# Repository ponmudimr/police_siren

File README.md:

## My 5-Day Launch into PCB Design 🚀

This project was a rapid, hands-on journey from theory to a physical product. Here's a log of how I designed and built my first custom PCB from scratch, with photos from each stage of the process.

---

### **Day 1: Unlocking the Lab! 🔑**
The journey began by conquering the basics. I passed the foundational electronics tests, which felt like beating a final boss to unlock the ultimate prize: **full access to the PCB & Fabrication lab**. The real adventure was about to start.

---

### **Day 2: Discovering the World of PCBs 💡**
Next, I dove into the theory of **Printed Circuit Boards (PCBs)**. I learned how these essential components are the hidden skeletons inside every gadget we use, providing the foundation for all the electronics.

---

### **Day 3: Architecting the Schematic 📝**
It was time to become an architect for electricity. Using **KiCad**, I designed the **schematic layout**. This is the foundational blueprint that shows how every single component connects logically, serving as the master plan for the circuit.

*The final schematic design for the police siren circuit.*

---

### **Day 4: Drawing the Copper Highways 🗺️**
With the blueprint done, I moved on to the physical design. This involved assigning **footprints** (the physical pads where components will sit) and then carefully routing the **traces** (the copper pathways connecting them). This is where the board takes its final shape.

*The final PCB layout in KiCad, showing all the copper traces ready for fabrication.*

---

### **Day 5: The Magic of Fabrication 🔥**
This was the most exciting part! I took my finished design files to the lab and watched as the machine **fabricated the board**. Seeing a digital design get etched into a physical copper-clad board was the perfect reward for all the hard work.

*The freshly fabricated board, ready for soldering!*

---

### **Day 6: Assembly, Soldering & Testing 🛠️⚡**

After fabrication, it was time to bring my design to life!  
Before soldering the components, I practiced on a dot board to get better control over my iron and verify the circuit’s working.

*My practice prototype on a dot board, which helped me verify the circuit and improve my soldering skills.*

Once confident, I moved on to the actual PCB and soldered each component — **resistors, LEDs, ICs, capacitors** — with precision and care.  
After assembly, I powered it on for the first test… and the **LEDs blinked perfectly** as per my design! That moment proved every step of the process was successful.

*The final assembled PCB after soldering — fully functional and glowing LEDs!*

---

### **Results Summary ✅**

| Stage | Status | Description |
|:------|:--------|:------------|
| Schematic Design | ✔️ | Completed in KiCad |
| PCB Layout | ✔️ | Verified with DRC |
| Fabrication | ✔️ | Successfully etched and drilled |
| Soldering | ✔️ | Components soldered neatly |
| Testing | ⚡ | Circuit fully functional |

---

### **What I Learned 🧠**

- PCB Design workflow using **KiCad**  
- Component placement, routing, and layout rules  
- Hands-on **fabrication and soldering techniques**  
- Debugging circuits and verifying outputs  
- How patience and precision make great PCBs  

---

### **Next Step 🔮**
This is just the beginning! I’m planning to:  
- Add a **microcontroller (Arduino/ATtiny)** for programmable siren patterns  
- Integrate **sound output**  
- Try designing a **double-layer PCB**

---

> “From schematic lines to glowing LEDs — my first PCB journey is complete!” 🌟

**Ponmudi M.R**  
_Electronics and Communication Engineering_  
_Bannari Amman Institute of Technology_

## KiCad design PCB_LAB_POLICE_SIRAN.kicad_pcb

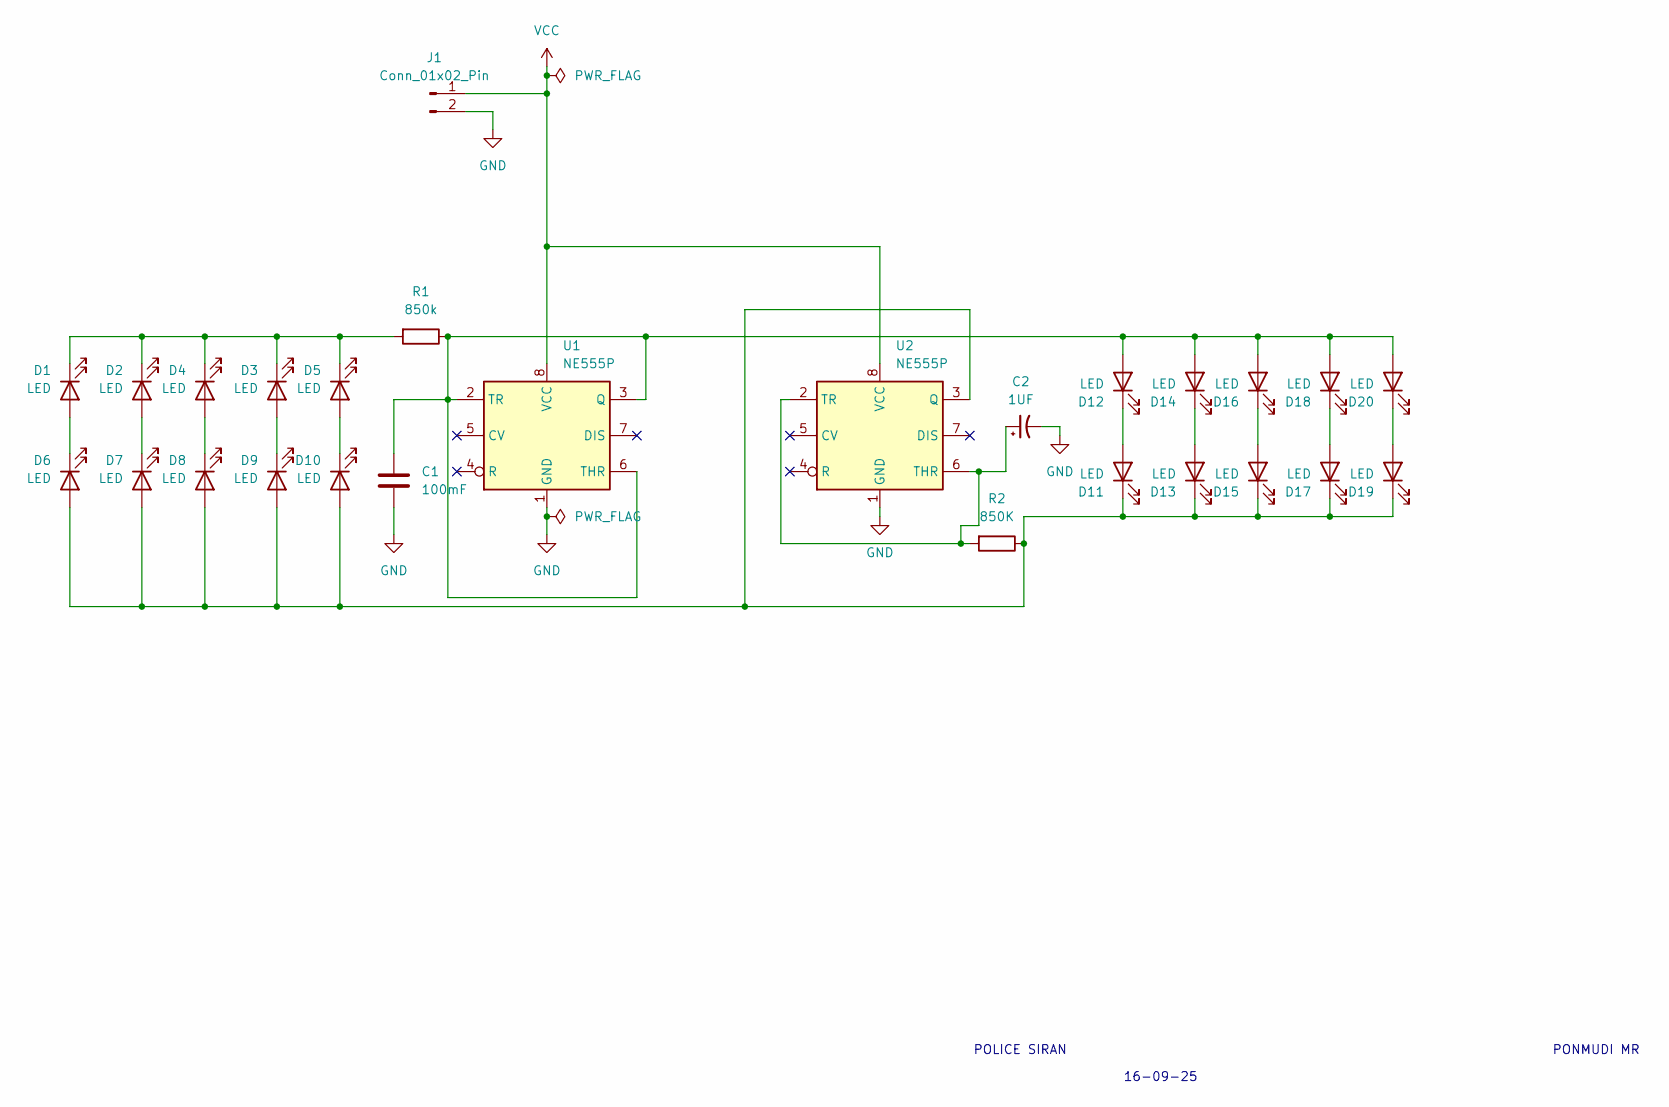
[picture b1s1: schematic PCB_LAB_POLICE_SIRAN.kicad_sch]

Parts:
C1: 100mF; CP_Radial_D5.0mm_P2.50mm
C2: 1UF; CP_Radial_D5.0mm_P2.50mm
D1, D2, D3, D4, D5, D6, D7, D8, D9, D10, D11, D12, D13, D14, D15, D16, D17, D18, D19, D20: LED; LED_D5.0mm
J1: Conn_01x02_Pin; PinSocket_1x02_P2.54mm_Vertical
R1: 850k; R_Axial_DIN0204_L3.6mm_D1.6mm_P5.08mm_Horizontal
R2: 850K; R_Axial_DIN0204_L3.6mm_D1.6mm_P5.08mm_Horizontal
U1, U2: NE555P; DIP-8_W7.62mm

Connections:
GND: C1.2, C2.2, J1.2, U1.1 (GND), U2.1 (GND)
unnamed: D1.2 (A), D6.1 (K)
unnamed: D1.1 (K), D2.1 (K), D3.1 (K), D4.1 (K), D5.1 (K), R1.2
unnamed: D2.2 (A), D7.1 (K)
unnamed: D3.2 (A), D9.1 (K)
unnamed: D4.2 (A), D8.1 (K)
unnamed: D6.2 (A), D7.2 (A), D8.2 (A), D9.2 (A), D10.2 (A), D11.1 (K), D13.1 (K), D15.1 (K), D17.1 (K), D19.1 (K), R2.1, U2.3 (Q)
unnamed: D5.2 (A), D10.1 (K)
unnamed: D11.2 (A), D12.1 (K)
unnamed: C1.1, D12.2 (A), D14.2 (A), D16.2 (A), D18.2 (A), D20.2 (A), R1.1, U1.2 (TR), U1.3 (Q), U1.6 (THR)
unnamed: D13.2 (A), D14.1 (K)
unnamed: D15.2 (A), D16.1 (K)
unnamed: D17.2 (A), D18.1 (K)
unnamed: D19.2 (A), D20.1 (K)
unnamed: C2.1, R2.2, U2.2 (TR), U2.6 (THR)
VCC: J1.1, U1.8 (VCC), U2.8 (VCC)

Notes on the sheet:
16-09-25
PONMUDI MR
POLICE SIRAN

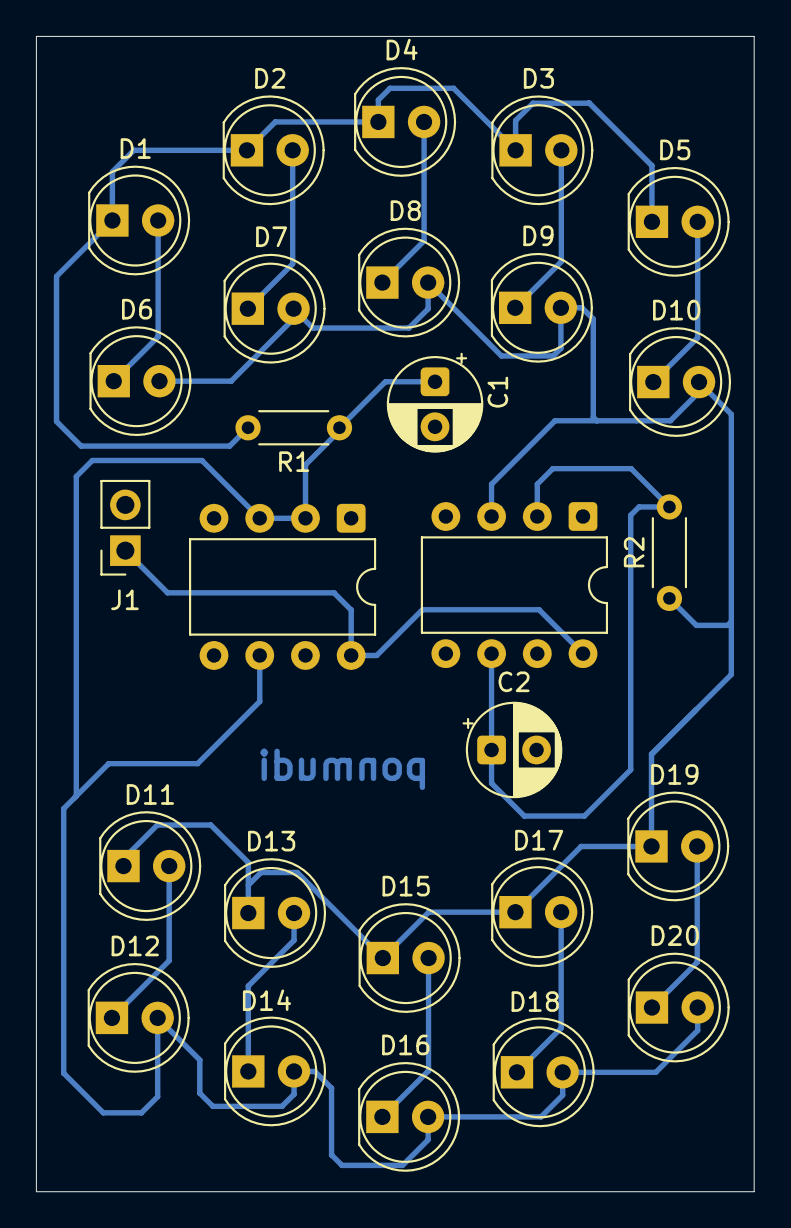
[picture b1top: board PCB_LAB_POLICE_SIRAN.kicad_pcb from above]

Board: 2 copper layers, 39.9 x 64.2 mm, 27 parts (0 on the bottom side), 16 nets.

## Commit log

2025-10-11 Create Pons
2025-10-11 POLICE_SIREN.md
2025-10-11 Added the project file,schematic and pcb
2025-11-11 README.md
